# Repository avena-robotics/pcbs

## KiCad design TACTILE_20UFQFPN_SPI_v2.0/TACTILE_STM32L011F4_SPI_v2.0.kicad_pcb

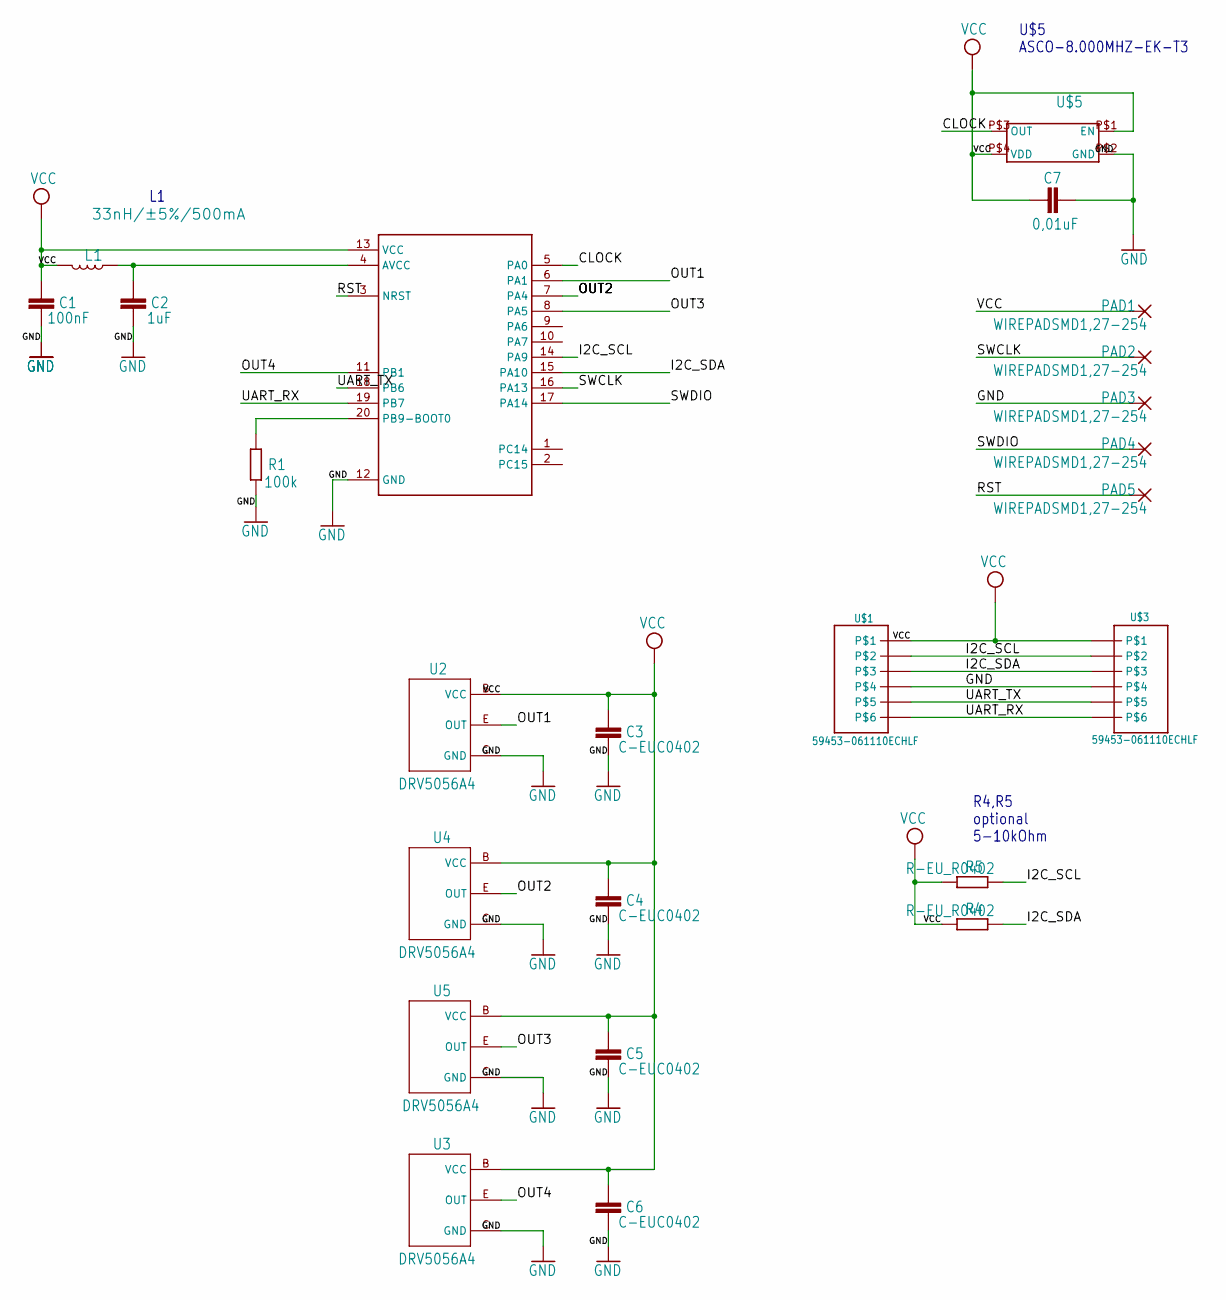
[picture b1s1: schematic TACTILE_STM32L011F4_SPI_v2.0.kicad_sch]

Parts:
C1: 100nF; C0402
C2: 1uF; C0402
C3, C4, C5, C6: C-EUC0402; C0402
C7: 0,01uF; C0402
L1: 33nH/±5%/500mA; 0603
PAD1, PAD2, PAD3, PAD4, PAD5: WIREPADSMD1,27-254; SMD1,27-2,54
R1: 100k; R0402
R4, R5: R-EU_R0402; R0402
U2, U3, U4, U5: DRV5056A4; SOT23-BEC
U$1, U$3: 59453-061110ECHLF
U$2: STM32L011F4; QFN50P300X300X60-20N
U$5: ASCO-8.000MHZ-EK-T3

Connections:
CLOCK: U$2.5 (PA0), U$5.P$3 (OUT)
GND: C1.2, C2.2, C3.2, C4.2, C5.2, C6.2, C7.1, PAD3.1, R1.1, U2.C (GND), U3.C (GND), U4.C (GND), U5.C (GND), U$1.P$4, U$2.12 (GND), U$3.P$4, U$5.P$2 (GND)
I2C_SCL: R5.1, U$1.P$2, U$2.14 (PA9), U$3.P$2
I2C_SDA: R4.1, U$1.P$3, U$2.15 (PA10), U$3.P$3
unnamed: C2.1, L1.1, U$2.4 (AVCC)
unnamed: R1.2, U$2.20 (PB9-BOOT0)
OUT1: U2.E (OUT), U$2.6 (PA1)
OUT2: U4.E (OUT), U$2.7 (PA4)
OUT3: U5.E (OUT), U$2.8 (PA5)
OUT4: U3.E (OUT), U$2.11 (PB1)
RST: PAD5.1, U$2.3 (NRST)
SWCLK: PAD2.1, U$2.16 (PA13)
SWDIO: PAD4.1, U$2.17 (PA14)
UART_RX: U$1.P$6, U$2.19 (PB7), U$3.P$6
UART_TX: U$1.P$5, U$2.18 (PB6), U$3.P$5
VCC: C1.1, C3.1, C4.1, C5.1, C6.1, C7.2, L1.2, PAD1.1, R4.2, R5.2, U2.B (VCC), U3.B (VCC), U4.B (VCC), U5.B (VCC), U$1.P$1, U$2.13 (VCC), U$3.P$1, U$5.P$1 (EN), U$5.P$4 (VDD)

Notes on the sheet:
R4,R5 optional 5-10kOhm
U$5 ASCO-8.000MHZ-EK-T3

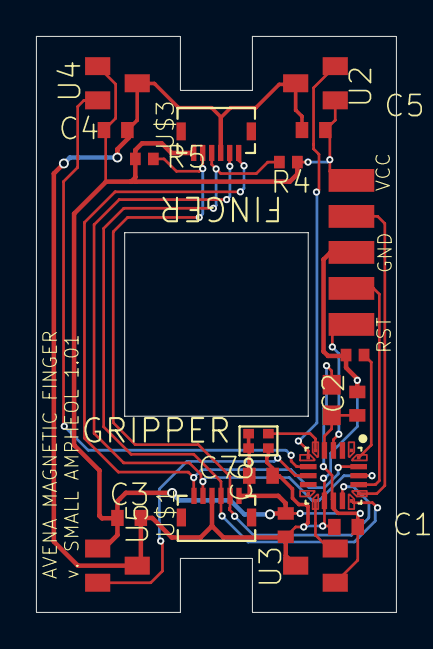
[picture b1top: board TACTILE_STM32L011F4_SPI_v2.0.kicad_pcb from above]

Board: 2 copper layers, 20.0 x 32.0 mm, 24 parts (0 on the bottom side), 16 nets.

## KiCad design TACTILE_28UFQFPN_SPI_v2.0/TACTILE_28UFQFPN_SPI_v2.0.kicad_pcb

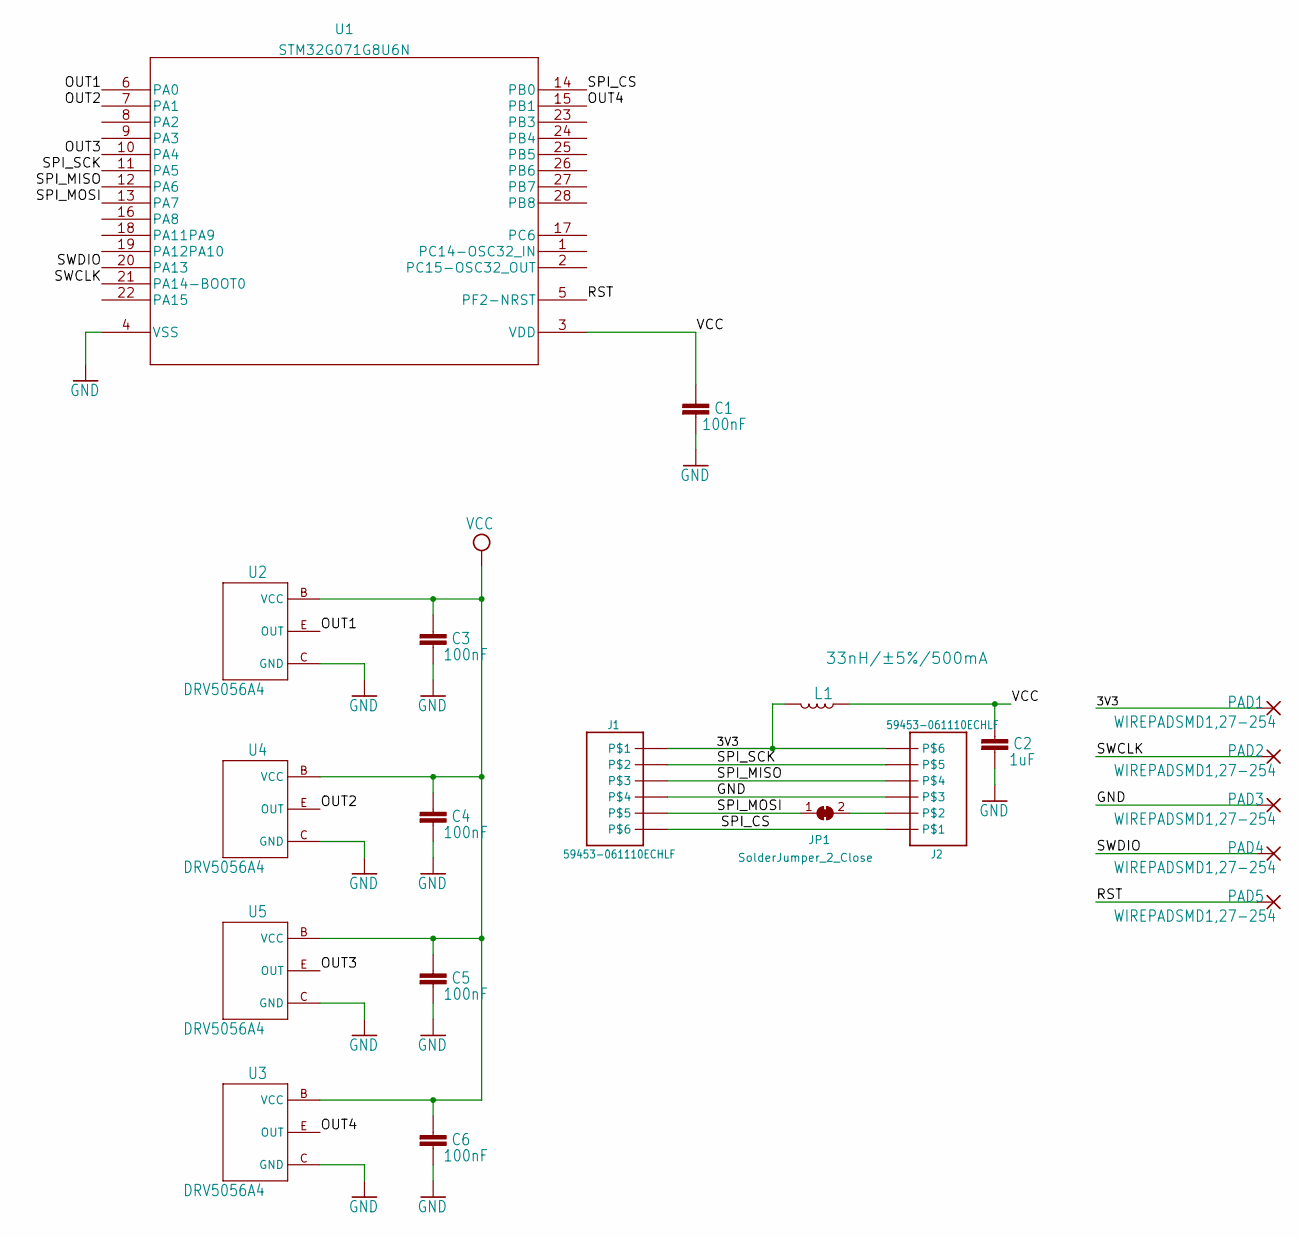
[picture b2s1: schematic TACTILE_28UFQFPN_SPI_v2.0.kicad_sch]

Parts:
C1, C3, C4, C5, C6: 100nF; C_0402_1005Metric_Pad0.74x0.62mm_HandSolder
C2: 1uF; C_0402_1005Metric_Pad0.74x0.62mm_HandSolder
J1, J2: 59453-061110ECHLF
JP1: SolderJumper_2_Close; SolderJumper-2_P1.3mm_Bridged_Pad1.0x1.5mm
L1: 33nH/±5%/500mA; L_0603_1608Metric_Pad1.05x0.95mm_HandSolder
PAD1, PAD2, PAD3, PAD4, PAD5: WIREPADSMD1,27-254; SMD1,27-2,54
U1: STM32G071G8U6N
U2, U3, U4, U5: DRV5056A4; SOT23-BEC

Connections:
/3V3: J1.P$1, J2.P$6, L1.2, PAD1.1
/OUT1: U1.6 (PA0), U2.E (OUT)
/OUT2: U1.7 (PA1), U4.E (OUT)
/OUT3: U1.10 (PA4), U5.E (OUT)
/OUT4: U1.15 (PB1), U3.E (OUT)
/RST: PAD5.1, U1.5 (PF2-NRST)
/SPI_CS: J1.P$6, J2.P$1, U1.14 (PB0)
/SPI_MISO: J1.P$3, J2.P$4, U1.12 (PA6)
/SPI_MOSI: J1.P$5, JP1.1 (A), U1.13 (PA7)
/SPI_SCK: J1.P$2, J2.P$5, U1.11 (PA5)
/SWCLK: PAD2.1, U1.21 (PA14-BOOT0)
/SWDIO: PAD4.1, U1.20 (PA13)
GND: C1.2, C2.2, C3.2, C4.2, C5.2, C6.2, J1.P$4, J2.P$3, PAD3.1, U1.4 (VSS), U2.C (GND), U3.C (GND), U4.C (GND), U5.C (GND)
unnamed: J2.P$2, JP1.2 (B)
VCC: C1.1, C2.1, C3.1, C4.1, C5.1, C6.1, L1.1, U1.3 (VDD), U2.B (VCC), U3.B (VCC), U4.B (VCC), U5.B (VCC)

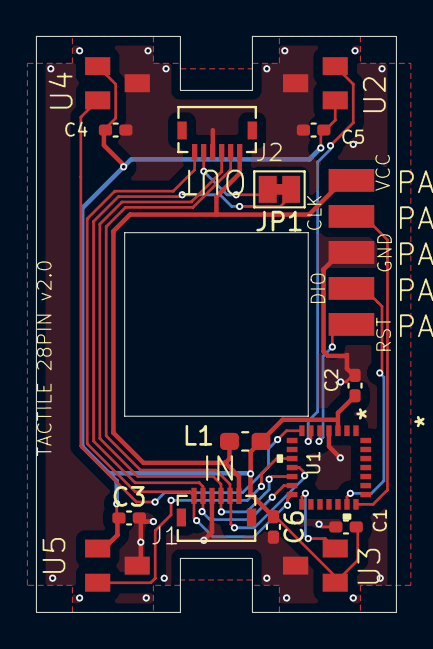
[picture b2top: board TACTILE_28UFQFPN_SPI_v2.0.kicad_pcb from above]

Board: 2 copper layers, 20.0 x 32.0 mm, 20 parts (0 on the bottom side), 15 nets.

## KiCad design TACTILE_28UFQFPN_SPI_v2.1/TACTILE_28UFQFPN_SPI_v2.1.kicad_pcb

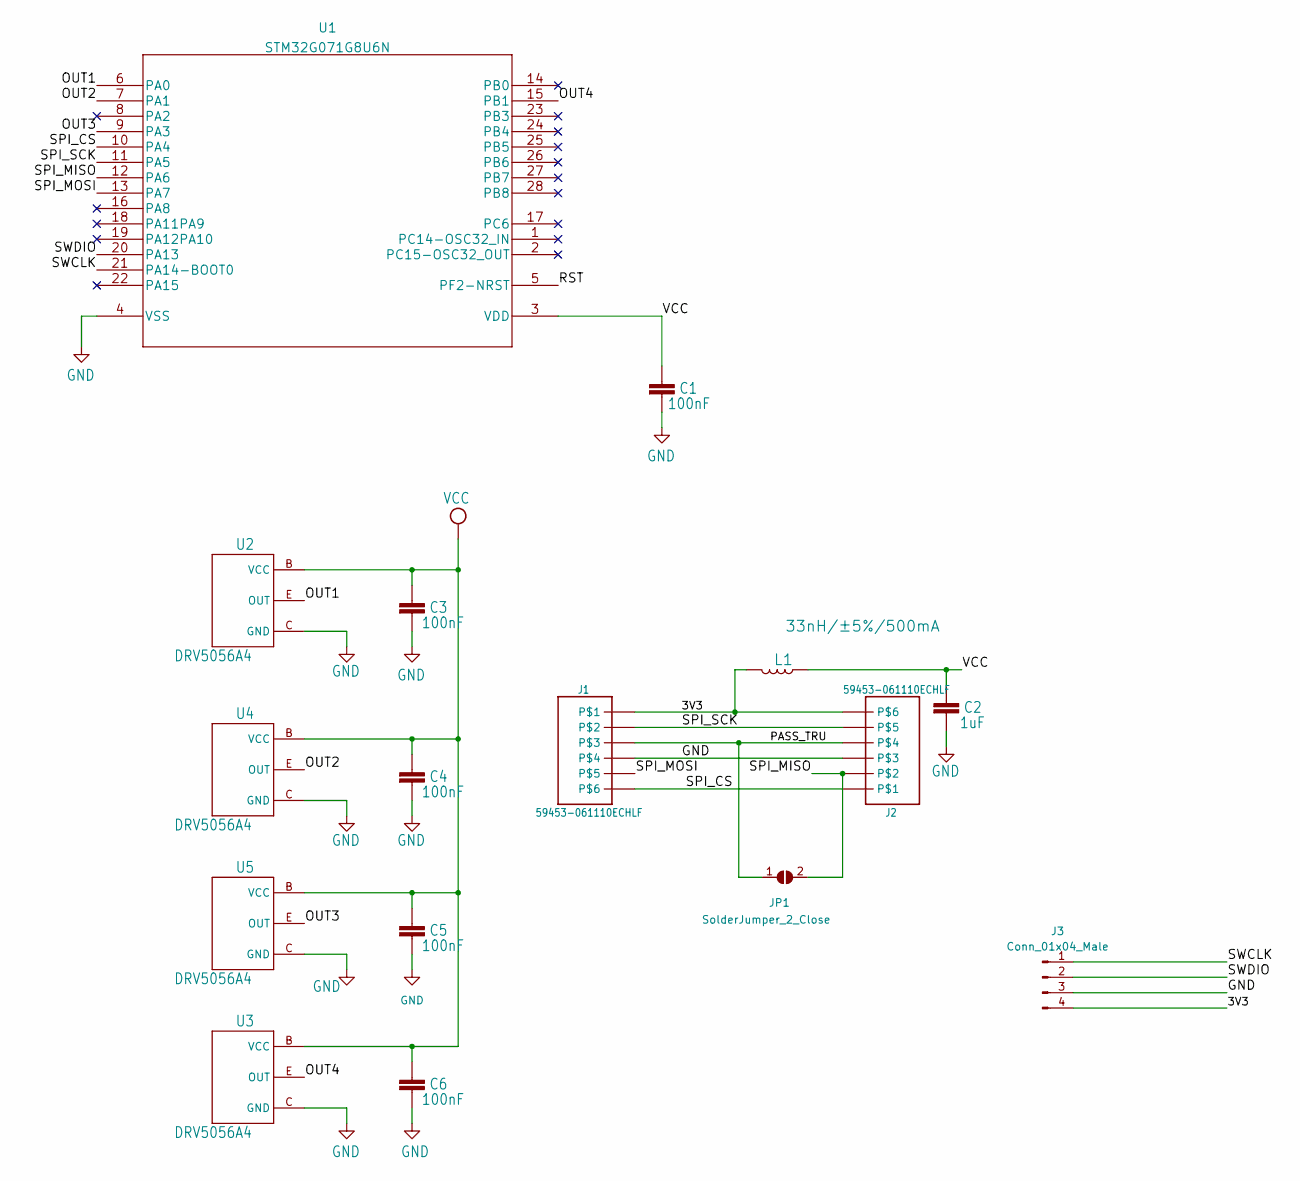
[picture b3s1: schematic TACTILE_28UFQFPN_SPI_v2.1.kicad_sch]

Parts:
C1, C3, C4, C5, C6: 100nF; C_0603_1608Metric_Pad1.08x0.95mm_HandSolder
C2: 1uF; C_0603_1608Metric_Pad1.08x0.95mm_HandSolder
J1, J2: 59453-061110ECHLF
J3: Conn_01x04_Male; PinHeader_1x04_P2.54mm_Vertical
JP1: SolderJumper_2_Close; SolderJumper-2_P1.3mm_Bridged_Pad1.0x1.5mm
L1: 33nH/±5%/500mA; L_0603_1608Metric_Pad1.05x0.95mm_HandSolder
U1: STM32G071G8U6N
U2, U3, U4, U5: DRV5056A4; SOT23-BEC

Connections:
/3V3: J1.P$1, J2.P$6, J3.4, L1.2
/OUT1: U1.6 (PA0), U2.E (OUT)
/OUT2: U1.7 (PA1), U4.E (OUT)
/OUT3: U1.9 (PA3), U5.E (OUT)
/OUT4: U1.15 (PB1), U3.E (OUT)
/PASS_TRU: J1.P$3, J2.P$4, JP1.1 (A)
/RST: U1.5 (PF2-NRST)
/SPI_CS: J1.P$6, J2.P$1, U1.10 (PA4)
/SPI_MISO: J2.P$2, JP1.2 (B), U1.12 (PA6)
/SPI_MOSI: J1.P$5, U1.13 (PA7)
/SPI_SCK: J1.P$2, J2.P$5, U1.11 (PA5)
/SWCLK: J3.1, U1.21 (PA14-BOOT0)
/SWDIO: J3.2, U1.20 (PA13)
GND: C1.2, C2.2, C3.2, C4.2, C5.2, C6.2, J1.P$4, J2.P$3, J3.3, U1.4 (VSS), U2.C (GND), U3.C (GND), U4.C (GND), U5.C (GND)
VCC: C1.1, C2.1, C3.1, C4.1, C5.1, C6.1, L1.1, U1.3 (VDD), U2.B (VCC), U3.B (VCC), U4.B (VCC), U5.B (VCC)

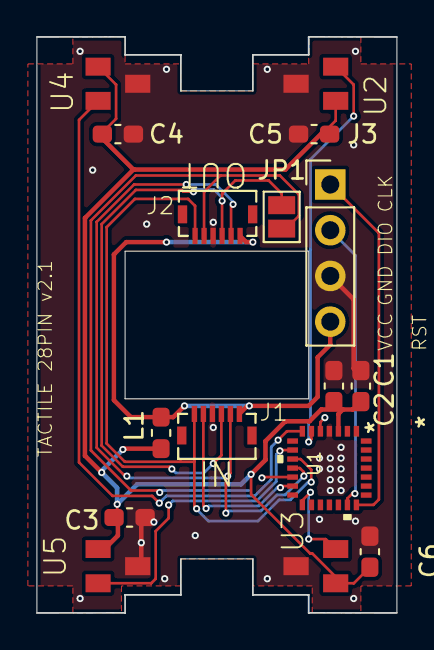
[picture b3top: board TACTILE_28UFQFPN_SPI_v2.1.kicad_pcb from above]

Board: 2 copper layers, 20.0 x 32.0 mm, 16 parts (0 on the bottom side), 14 nets.

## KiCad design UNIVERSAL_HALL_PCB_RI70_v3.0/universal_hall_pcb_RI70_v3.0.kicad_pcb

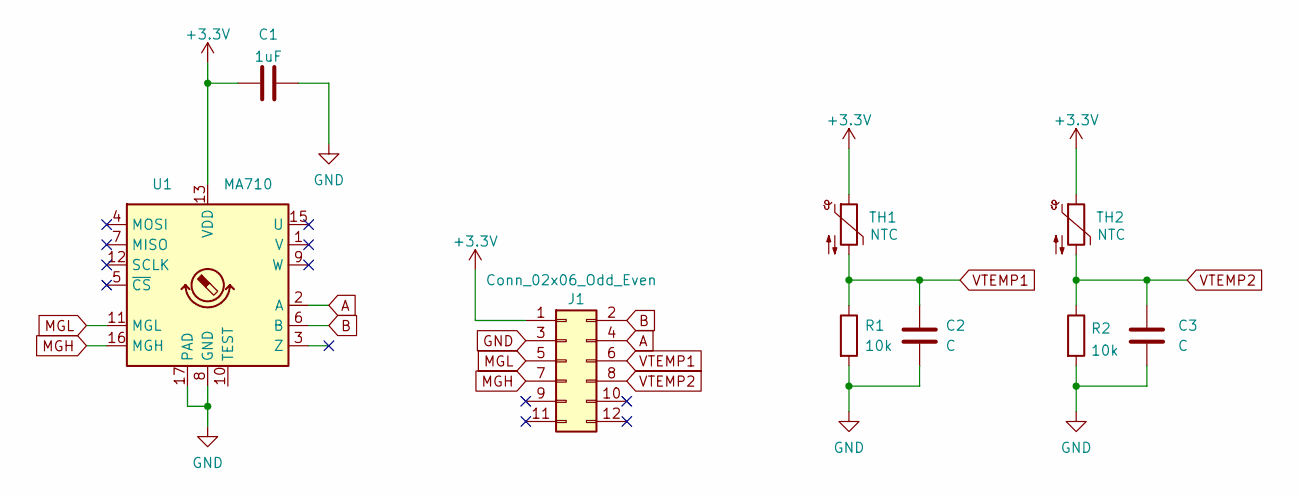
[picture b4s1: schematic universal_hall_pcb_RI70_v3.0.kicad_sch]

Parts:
C1: 1uF; C_0603_1608Metric_Pad1.08x0.95mm_HandSolder
C2, C3: C; C_0603_1608Metric_Pad1.08x0.95mm_HandSolder
J1: Conn_02x06_Odd_Even; PinHeader_2x06_P2.54mm_Vertical
R1, R2: 10k; R_0603_1608Metric_Pad0.98x0.95mm_HandSolder
TH1, TH2: NTC; PinHeader_1x02_P2.54mm_Vertical
U1: MA710; VQFN-16-1EP_3x3mm_P0.5mm_EP1.8x1.8mm

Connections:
+3V3: C1.1, J1.1, TH1.1, TH2.1, U1.13 (VDD)
A: J1.4, U1.2 (A)
B: J1.2, U1.6 (B)
GND: C1.2, C2.2, C3.2, J1.3, R1.2, R2.2, U1.8 (GND), U1.17 (PAD)
MGH: J1.7, U1.16 (MGH)
MGL: J1.5, U1.11 (MGL)
VTEMP1: C2.1, J1.6, R1.1, TH1.2
VTEMP2: C3.1, J1.8, R2.1, TH2.2

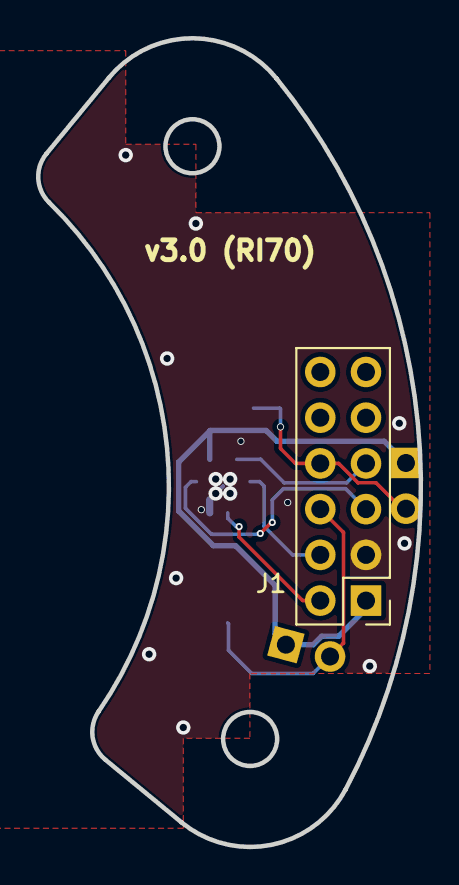
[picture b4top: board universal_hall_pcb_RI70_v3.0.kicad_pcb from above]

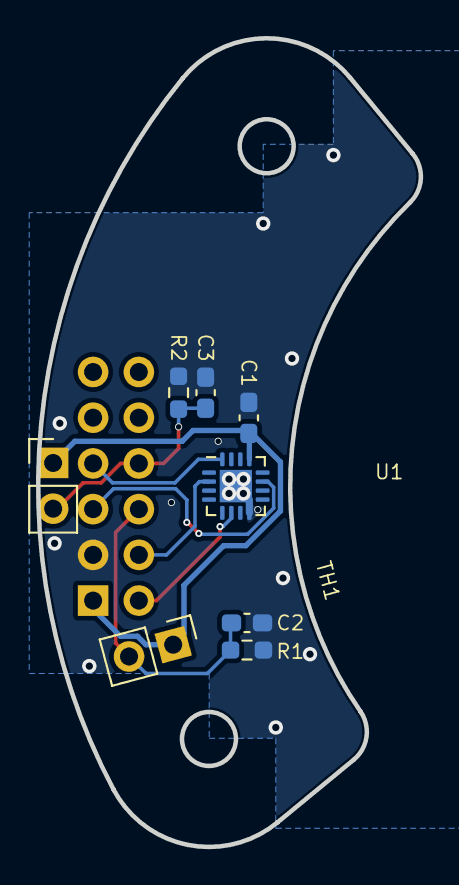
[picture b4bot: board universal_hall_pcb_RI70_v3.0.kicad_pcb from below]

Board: 2 copper layers, 21.3 x 44.9 mm, 9 parts (8 on the bottom side), 8 nets.

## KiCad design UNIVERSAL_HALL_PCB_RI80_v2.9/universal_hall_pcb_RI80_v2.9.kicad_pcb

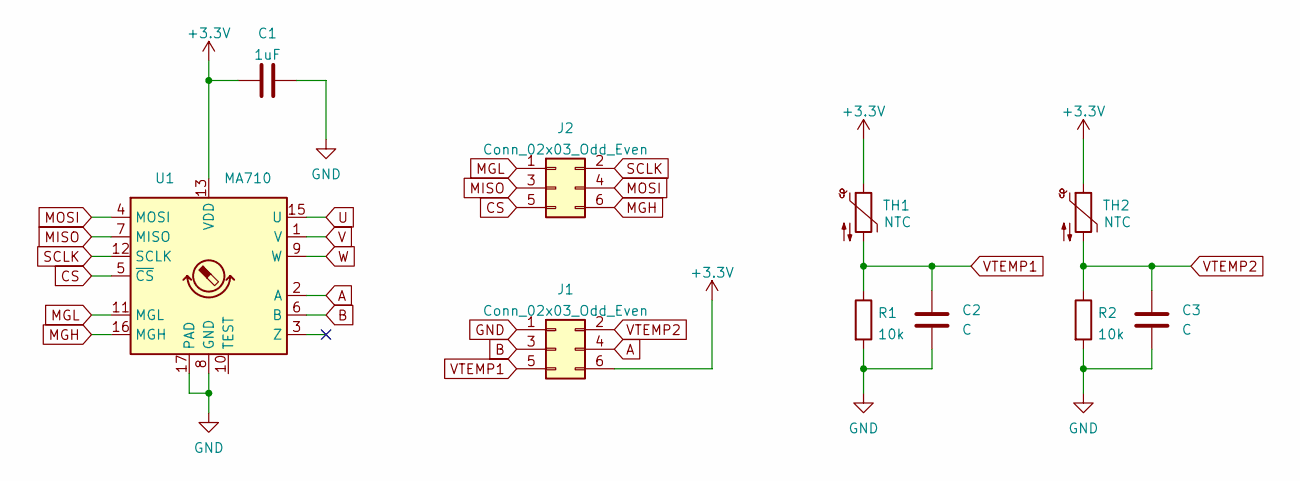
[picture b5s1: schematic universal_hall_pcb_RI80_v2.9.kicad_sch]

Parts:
C1: 1uF; C_0603_1608Metric_Pad1.08x0.95mm_HandSolder
C2, C3: C; C_0603_1608Metric_Pad1.08x0.95mm_HandSolder
J1, J2: Conn_02x03_Odd_Even; PinSocket_2x03_P2.54mm_Vertical
R1, R2: 10k; R_0603_1608Metric_Pad0.98x0.95mm_HandSolder
TH1, TH2: NTC; PinHeader_1x02_P2.54mm_Vertical
U1: MA710; VQFN-16-1EP_3x3mm_P0.5mm_EP1.8x1.8mm

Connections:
+3V3: C1.1, J1.6, TH1.1, TH2.1, U1.13 (VDD)
A: J1.4, U1.2 (A)
B: J1.3, U1.6 (B)
CS: J2.5, U1.5 (~CS)
GND: C1.2, C2.2, C3.2, J1.1, R1.2, R2.2, U1.8 (GND), U1.17 (PAD)
MGH: J2.6, U1.16 (MGH)
MGL: J2.1, U1.11 (MGL)
MISO: J2.3, U1.7 (MISO)
MOSI: J2.4, U1.4 (MOSI)
SCLK: J2.2, U1.12 (SCLK)
U: U1.15 (U)
V: U1.1 (V)
VTEMP1: C2.1, J1.5, R1.1, TH1.2
VTEMP2: C3.1, J1.2, R2.1, TH2.2
W: U1.9 (W)

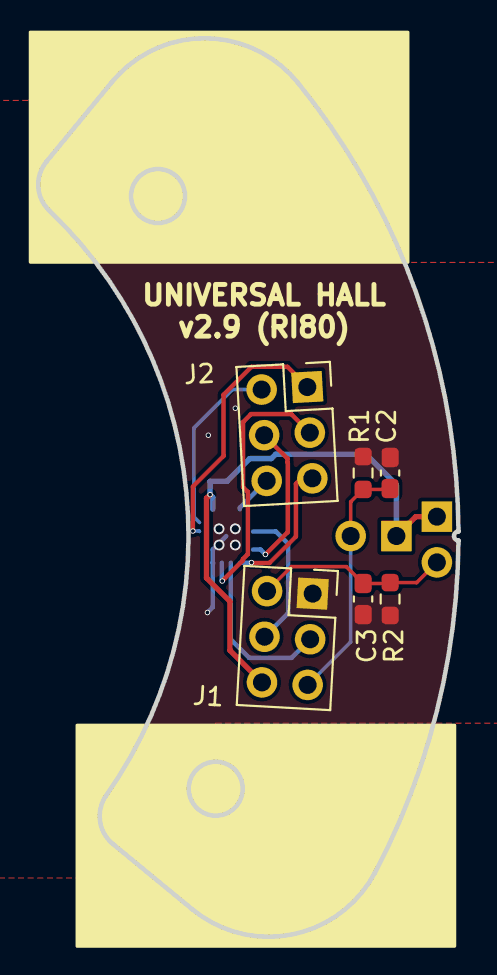
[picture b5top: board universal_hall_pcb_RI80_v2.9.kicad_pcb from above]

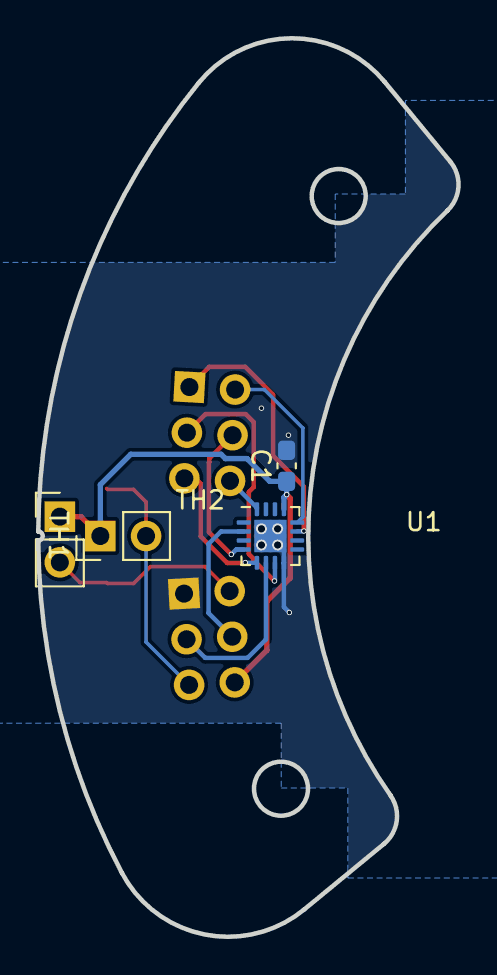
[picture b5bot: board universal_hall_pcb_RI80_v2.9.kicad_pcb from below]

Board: 2 copper layers, 23.3 x 49.9 mm, 10 parts (4 on the bottom side), 12 nets.

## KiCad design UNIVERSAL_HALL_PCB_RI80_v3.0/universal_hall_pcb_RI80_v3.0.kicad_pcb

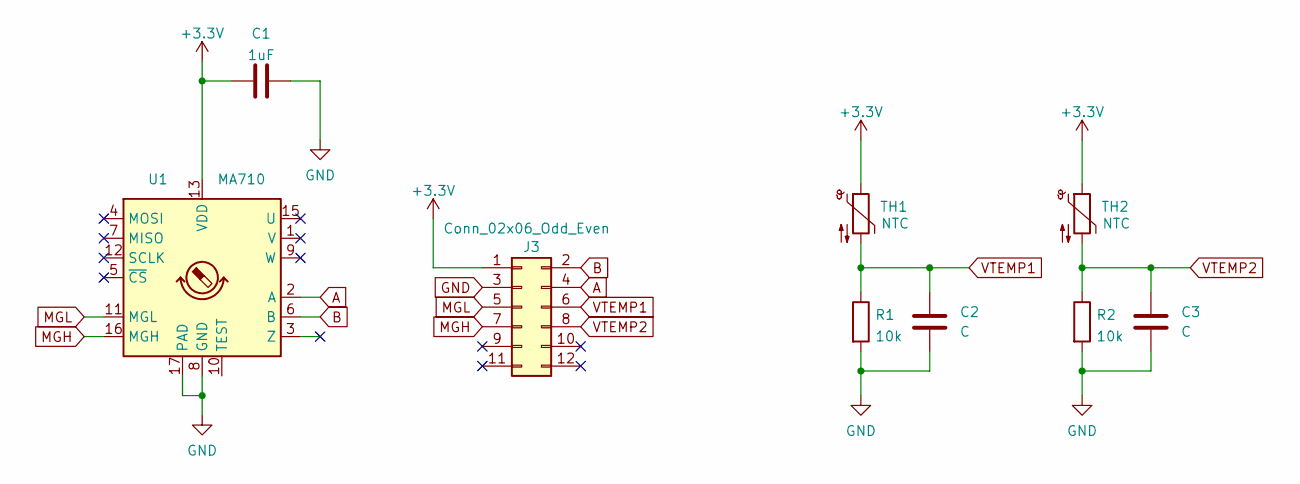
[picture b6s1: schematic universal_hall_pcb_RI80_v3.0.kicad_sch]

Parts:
C1: 1uF; C_0603_1608Metric_Pad1.08x0.95mm_HandSolder
C2, C3: C; C_0603_1608Metric_Pad1.08x0.95mm_HandSolder
J3: Conn_02x06_Odd_Even; PinHeader_2x06_P2.54mm_Vertical
R1, R2: 10k; R_0603_1608Metric_Pad0.98x0.95mm_HandSolder
TH1, TH2: NTC; PinHeader_1x02_P2.54mm_Vertical
U1: MA710; VQFN-16-1EP_3x3mm_P0.5mm_EP1.8x1.8mm

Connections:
+3V3: C1.1, J3.1, TH1.1, TH2.1, U1.13 (VDD)
A: J3.4, U1.2 (A)
B: J3.2, U1.6 (B)
GND: C1.2, C2.2, C3.2, J3.3, R1.2, R2.2, U1.8 (GND), U1.17 (PAD)
MGH: J3.7, U1.16 (MGH)
MGL: J3.5, U1.11 (MGL)
VTEMP1: C2.1, J3.6, R1.1, TH1.2
VTEMP2: C3.1, J3.8, R2.1, TH2.2

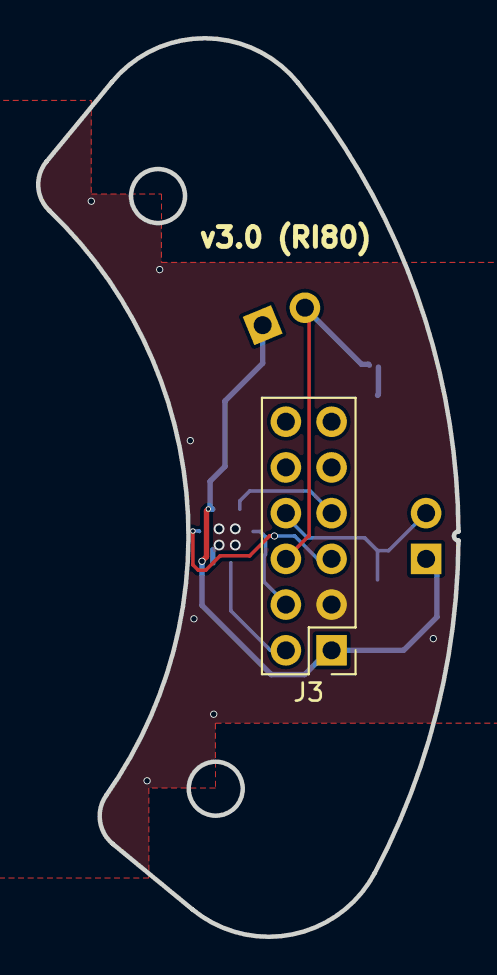
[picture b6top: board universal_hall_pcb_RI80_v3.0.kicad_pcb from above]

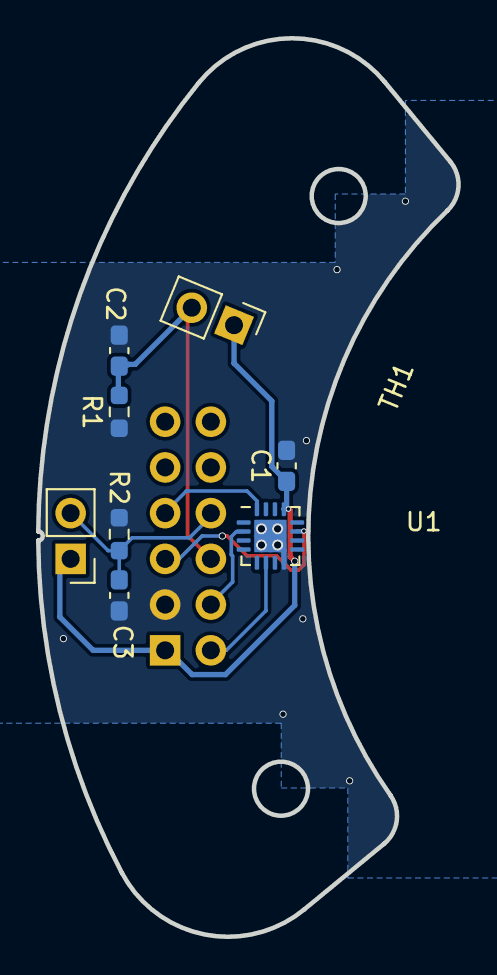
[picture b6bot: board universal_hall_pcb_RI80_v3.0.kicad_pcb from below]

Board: 2 copper layers, 23.3 x 49.9 mm, 9 parts (8 on the bottom side), 8 nets.

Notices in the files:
parts and their libraries:
Copyright 2021 Accelerated Designs. All rights reserved.
